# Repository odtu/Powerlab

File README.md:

# powerlab
METU Powerlab File Repository

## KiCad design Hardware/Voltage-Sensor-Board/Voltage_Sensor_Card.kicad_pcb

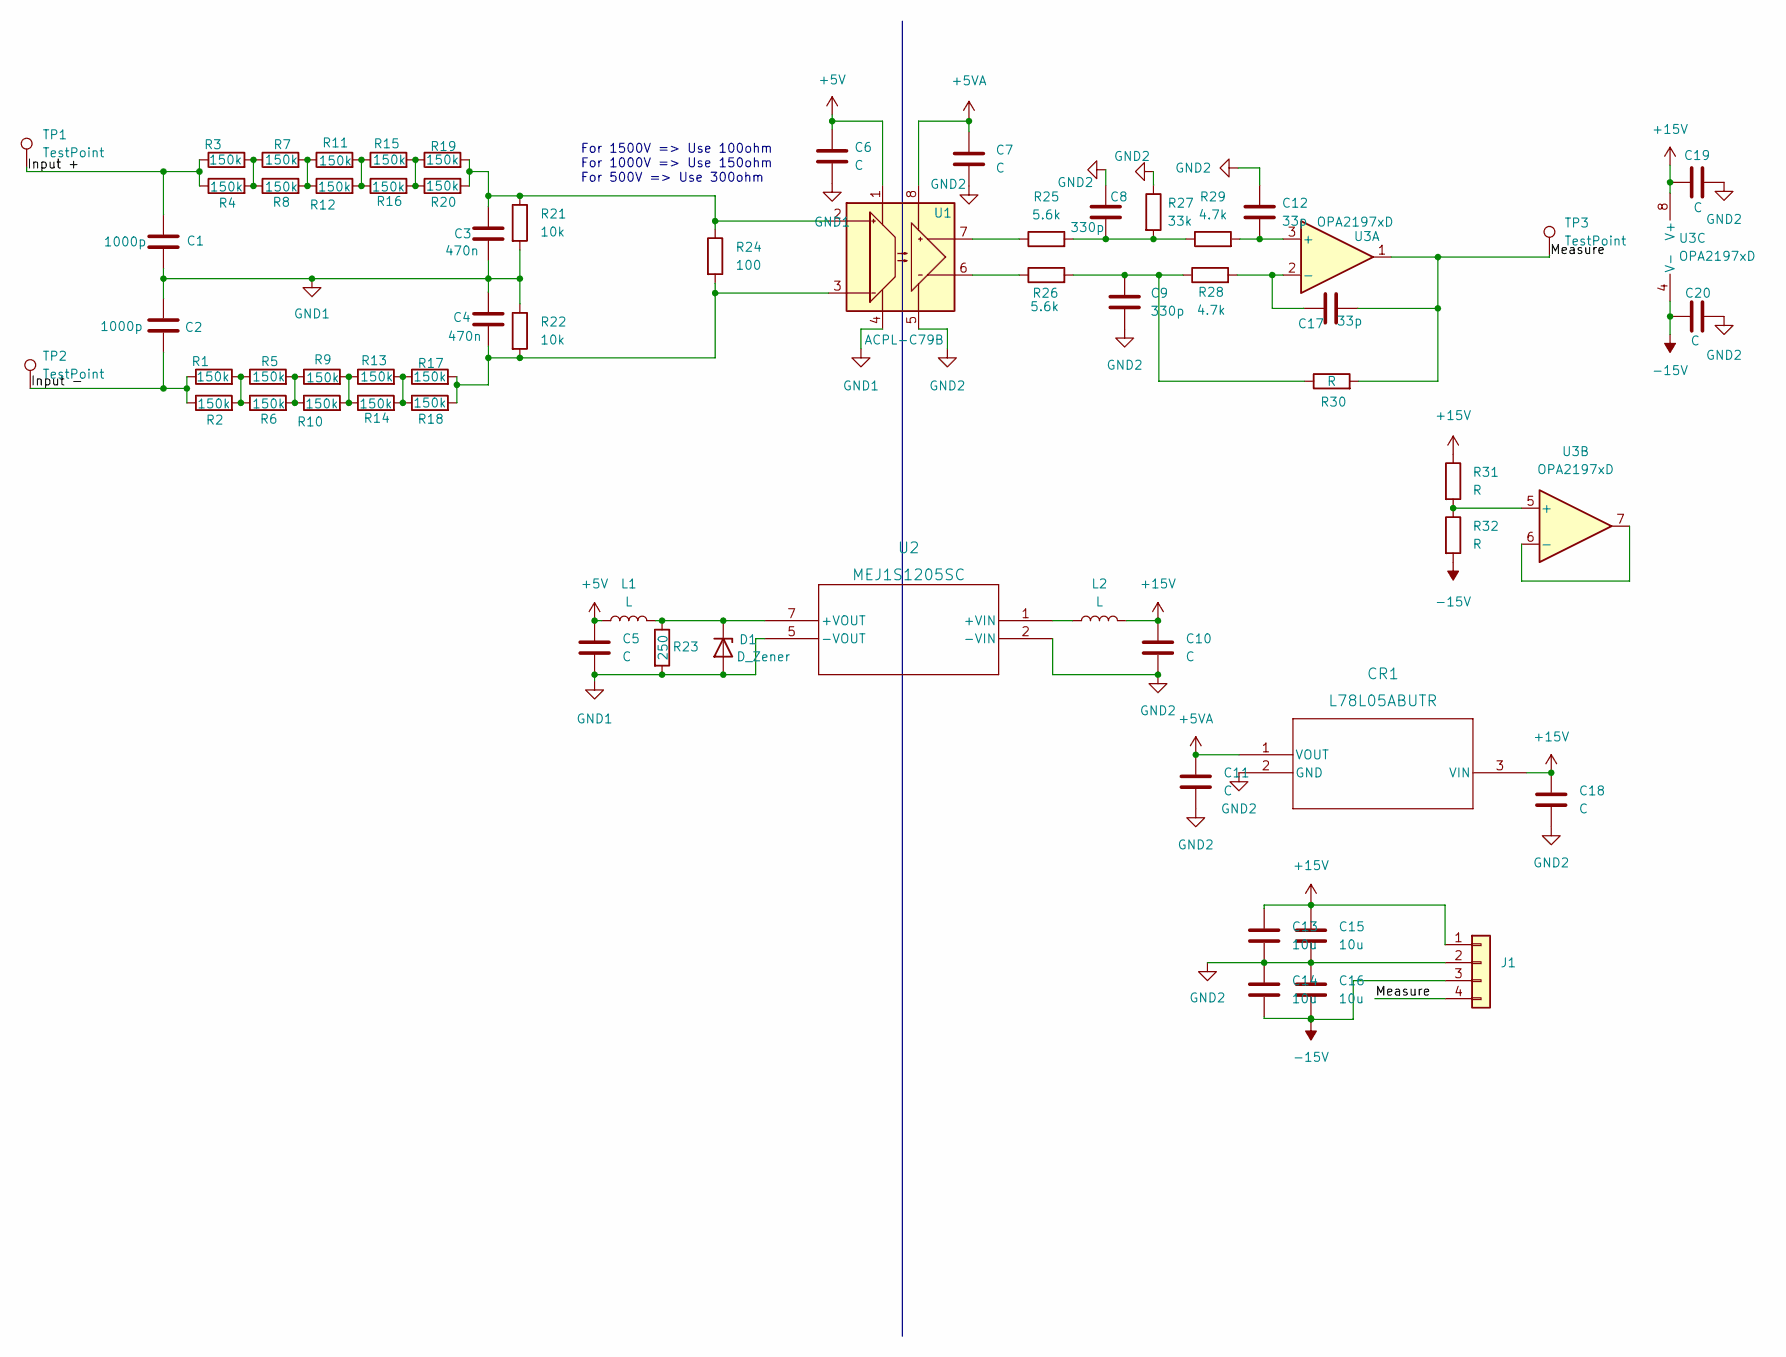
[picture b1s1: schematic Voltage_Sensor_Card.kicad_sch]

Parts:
C1, C2: 1000p; C_1206_3216Metric
C3, C4: 470n; C_0603_1608Metric
C5, C6, C7, C10, C11, C18, C19, C20: C; C_0603_1608Metric
C8, C9: 330p; C_0603_1608Metric
C12, C17: 33p; C_0603_1608Metric
C13, C14, C15, C16: 10u; C_0805_2012Metric
CR1: L78L05ABUTR; SOT-89_STM
D1: D_Zener; D_0603_1608Metric
J1: (no value)
L1, L2: L; L_0603_1608Metric
R1, R2, R3, R4, R5, R6, R7, R8, R9, R10, R11, R12, R13, R14, R15, R16, R17, R18, R19, R20: 150k; R_1206_3216Metric
R21, R22: 10k; R_0603_1608Metric
R23: 250; R_0603_1608Metric
R24: 100; R_0603_1608Metric
R25, R26: 5.6k; R_0603_1608Metric
R27: 33k; R_0603_1608Metric
R28, R29: 4.7k; R_0603_1608Metric
R30, R31, R32: R; R_0603_1608Metric
TP1, TP2, TP3: TestPoint; TestPoint_Plated_Hole_D2.0mm
U1: ACPL-C79B; SSO-8_6.8x5.9mm_P1.27mm_Clearance8mm
U2: MEJ1S1205SC; SIP4_MEJ1S_MUR
U3: OPA2197xD; SOIC-8_3.9x4.9mm_P1.27mm

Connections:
+5V: C5.1, C6.1, L1.1, U1.1 (VDD1)
+5VA: C7.1, C11.1, CR1.1 (VOUT), U1.8 (VDD2)
+15V: C10.1, C13.1, C15.1, C18.1, C19.1, CR1.3 (VIN), J1.1, L2.2, R31.1, U3.8 (V+)
-15V: C14.2, C16.2, C20.1, J1.3, R32.2, U3.4 (V-)
/Input +: C1.1, R3.1, R4.1, TP1.1
/Input -: C2.2, R1.1, R2.1, TP2.1
/Measure: C17.2, J1.4, R30.2, TP3.1, U3.1
GND1: C1.2, C2.1, C3.2, C4.1, C5.2, C6.2, D1.2 (A), R21.2, R22.1, R23.2, U1.4 (GND1), U2.5 (-VOUT)
GND2: C7.2, C8.1, C9.2, C10.2, C11.2, C12.1, C13.2, C14.1, C15.2, C16.1, C18.2, C19.2, C20.2, CR1.2 (GND), J1.2, R27.1, U1.5 (GND2), U2.2 (-VIN)
unnamed: C3.1, R19.2, R20.2, R21.1, R24.1, U1.2 (IN+)
unnamed: C4.2, R17.2, R18.2, R22.2, R24.2, U1.3 (IN-)
unnamed: C8.2, R25.2, R27.2, R29.1
unnamed: C9.1, R26.2, R28.1, R30.1
unnamed: C12.2, R29.2, U3.3 (+)
unnamed: C17.1, R28.2, U3.2 (-)
unnamed: D1.1 (K), L1.2, R23.1, U2.7 (+VOUT)
unnamed: L2.1, U2.1 (+VIN)
unnamed: R1.2, R2.2, R5.1, R6.1
unnamed: R3.2, R4.2, R7.1, R8.1
unnamed: R5.2, R6.2, R9.1, R10.1
unnamed: R9.2, R10.2, R13.1, R14.1
unnamed: R7.2, R8.2, R11.1, R12.1
unnamed: R11.2, R12.2, R15.1, R16.1
unnamed: R13.2, R14.2, R17.1, R18.1
unnamed: R15.2, R16.2, R19.1, R20.1
unnamed: R25.1, U1.7 (OUT+)
unnamed: R26.1, U1.6 (OUT-)
unnamed: R31.2, R32.1, U3.5 (+)
unnamed: U3.6 (-), U3.7

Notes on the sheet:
For 1500V => Use 100ohm For 1000V => Use 150ohm For 500V => Use 300ohm

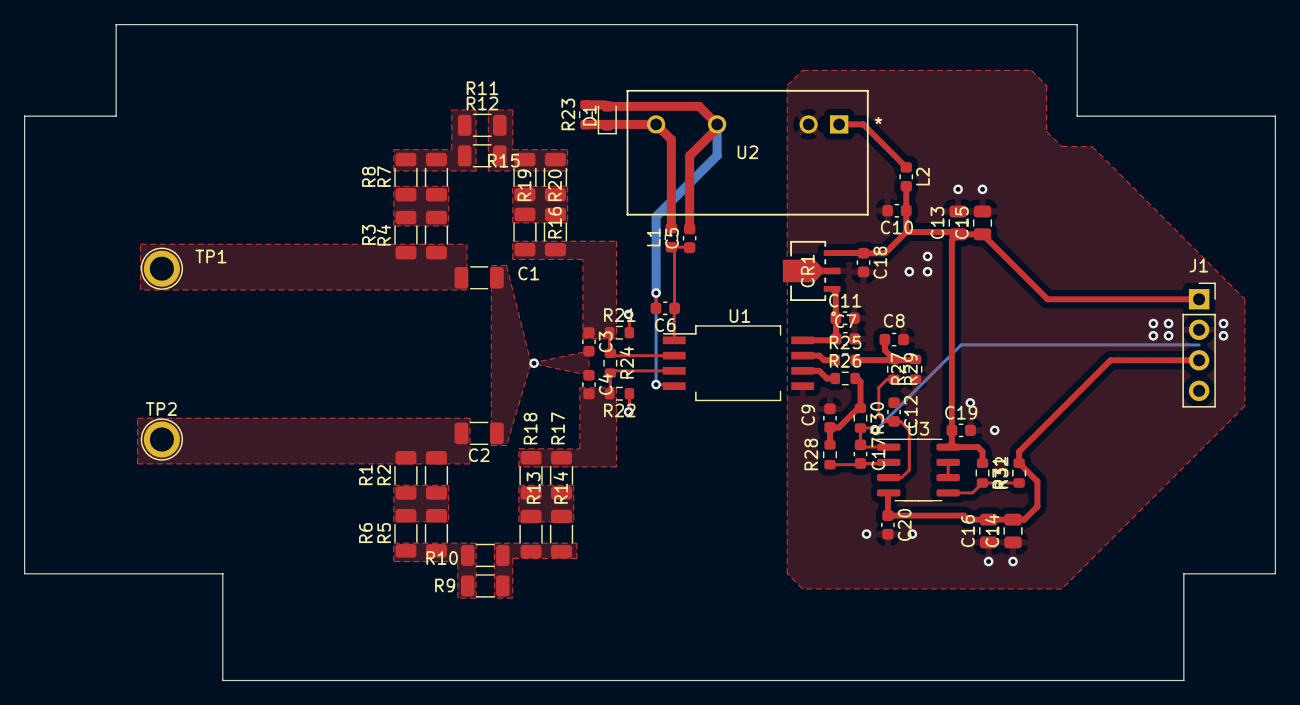
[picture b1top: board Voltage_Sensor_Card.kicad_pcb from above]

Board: 2 copper layers, 104.1 x 54.6 mm, 62 parts (0 on the bottom side), 29 nets.

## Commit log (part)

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2017-08-10 first files
2017-12-11 Old Seminars
2017-12-11 This week seminar announcements
2017-12-12 Seminar announcemnets final form
2017-12-18 Seminar announcment for seminar 10
2018-08-03 Add files via upload
    vectörel logo eklendi
2019-11-19 powerlab reposunun altına taşıdım.
    @ozank @UgurC Hocam Uğurcan seminerleri benim eski yerin altına eklemiş. Doğru repo burası değil mi neden 2 tane farklı repo var?
2019-11-26 Rename Conference and Transaction Due Dates to Conference_paper_due_dates.mdransaction Due Dates
2019-11-26 Rename Conference_paper_due_dates.mdransaction Due Dates to Conference_paper_due_dates.md
2020-02-04 Seminer sunumları
2020-02-04 seminer sunumlarının devamı
2020-02-06 yetki tanimlama
2020-02-06 makina labı yetki formu
2020-02-06 erişim prosedürü
2020-03-04 hande yetki
2020-03-04 hakan polat
2020-03-04 form update
2020-03-04 zgryzc
2020-03-04 gökhan siamak
2020-03-05 typo
2020-03-05 furkan emre
2020-03-06 Furkan dolap no
2020-03-06 kurallar güncellendi
2020-03-06 symbol try
2020-03-06 symbols
2020-03-10 ilker, mesut
2020-03-13 özgür
2020-03-24 giriş yetkileri
2020-07-01 hakan, siamak
2021-01-07 ogün altun
2021-03-01 paul
2021-06-14 soheil
2021-08-05 ışık, mümtaz
2021-10-07 samet
2021-10-21 yunus, emir
2021-10-21 ozgur mesai saati disi
2021-10-22 lab formu yazım hataları
2021-10-22 mohammad door lock
2021-10-27 Serhat anahtar verildi
2021-12-22 osman yücel
2022-01-31 mohammad dolap anahtarı
2022-05-13 yetki iptalleri
    çalışması biten kişiler çıkarıldı
2022-10-25 sahin
2022-11-07 TI C2000 Launchpad initializion guide is added
2022-11-15 kapıdaki uyarı dokümanı
2022-11-22 erdem
2023-03-27 Kemal Parlaktuna
2023-10-17 team update, ismail
2023-11-29 ahmetcan, ali
2024-02-06 mustafa burak
2024-02-21 tugay
2024-02-23 yunus cay tez dolabı
2024-02-23 yunus malzeme dolabı
2024-03-06 0402 resistor- sarf malzemeleri
2024-03-06 ICEM 2024 Extended
2024-04-02 Göktuğ
2024-04-17 Arda
2024-06-16 Tektronix MSO 4/5/6 LAN connection
2024-06-16 extension correction
2024-07-12 QNAP NAS Mac Address bug fix procedure
2024-08-23 Update tektronix-lan-connection.md
    the path should include the string after the username, "DESKTOP-QR4T\Desktop\mso" should be entered as "Desktop\mso"
2024-09-30 kaan
2024-10-06 Create Voltage-sensor-card
    Voltage-sensor-card file created.
2024-10-06 Added Differential Voltage Sensor PCB files.
    PCB Schematics are mostly completed, still working on the layout.
2024-10-06 Edited the layout.
    Layout is not finalized yet, needs to be revised with an experienced team member.
2024-10-09 Revized the layout.
    Changed the orientation and placement of components, added all tracks and copper pours.
2024-11-08 project list draft
2024-11-08 user list
2024-11-08 projects list
2024-11-09 Update README.md
    3 Phase Inverters project repository is added.
2024-11-09 taha
2024-11-09 w45 review
2024-11-11 ogün
2024-11-16 week 46 edits
2024-11-18 weekend
2024-11-25 week 47
2024-11-25 emojis
2024-12-01 week 48
2024-12-12 Emin
2024-12-15 week 50
2024-12-21 week 51
2024-12-26 0402 and 0603 Resistor Kit
2024-12-29 week 52
2024-12-29 folder structure organization and utility hardware/software
    closes #22 and #20
2025-01-05 commits
2025-01-20 2025 first commits
2025-01-23 Capacitor Kit 603 is added
2025-01-24 Terminal Symbolic link for Tektronix setup
2025-01-26 week3
2025-02-02 week 5
2025-02-03 XDS100v2 Emulator for TI Microprocessors
2025-02-09 week 6
2025-02-16 week 7
2025-02-23 week 8
2025-02-25 emre
2025-03-02 week 9
2025-03-09 week 10
2025-03-12 mach lab halid
2025-03-16 week 11
2025-03-17 Create Cinergia Documents
2025-03-18 Cinergia document partial upload
    25mb limit
2025-03-18 Cinergia Documents partial upload
    limit 25mb
2025-03-19 metin
2025-03-23 week 12
2025-03-30 week 13
2025-04-06 bayram week
2025-04-13 week 15
2025-04-21 2025 Q1 scores
2025-04-21 commit score list
2025-04-27 week 17
2025-05-04 week 18
2025-05-11 week 19
2025-06-04 sefer added, and team update
2025-08-18 Aytunc, Elif
2025-10-20 laser engraver driver and software
2025-12-10 pot min 3 mins (2 large cups) - pot max 15 mins (10 large cups)
2025-12-16 yazılım böcek sabitleme güncellemesi
2026-01-31 Majör donanım reformu
2026-03-03 Yetki ve Kurallar Markdown eklendi, öneriler eklenebilir
2026-03-03 Görünüm ve format iyileştirildi
2026-03-09 Revise user access and safety protocols in lab rules
    İki kişi çalışma için voltal limitleri eklendi
2026-03-11 Programming & Debugging Custom C2000 MCU Using Texas Launchpad (Launchxl-F280049C)
2026-03-27 yetki tanımları draft
2026-03-28 yetki draft 2
2026-04-08 giriş yetki iptal
2026-04-16 claude settings for motor drive project is added
    markdown files are added, rest will submitted soon
2026-06-26 göl, şahin öğrenciler
2026-06-26 ingilizce formlar, polat mesai disi
